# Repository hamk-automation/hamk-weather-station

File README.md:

# hamk-weather-station
cheap ass weather station

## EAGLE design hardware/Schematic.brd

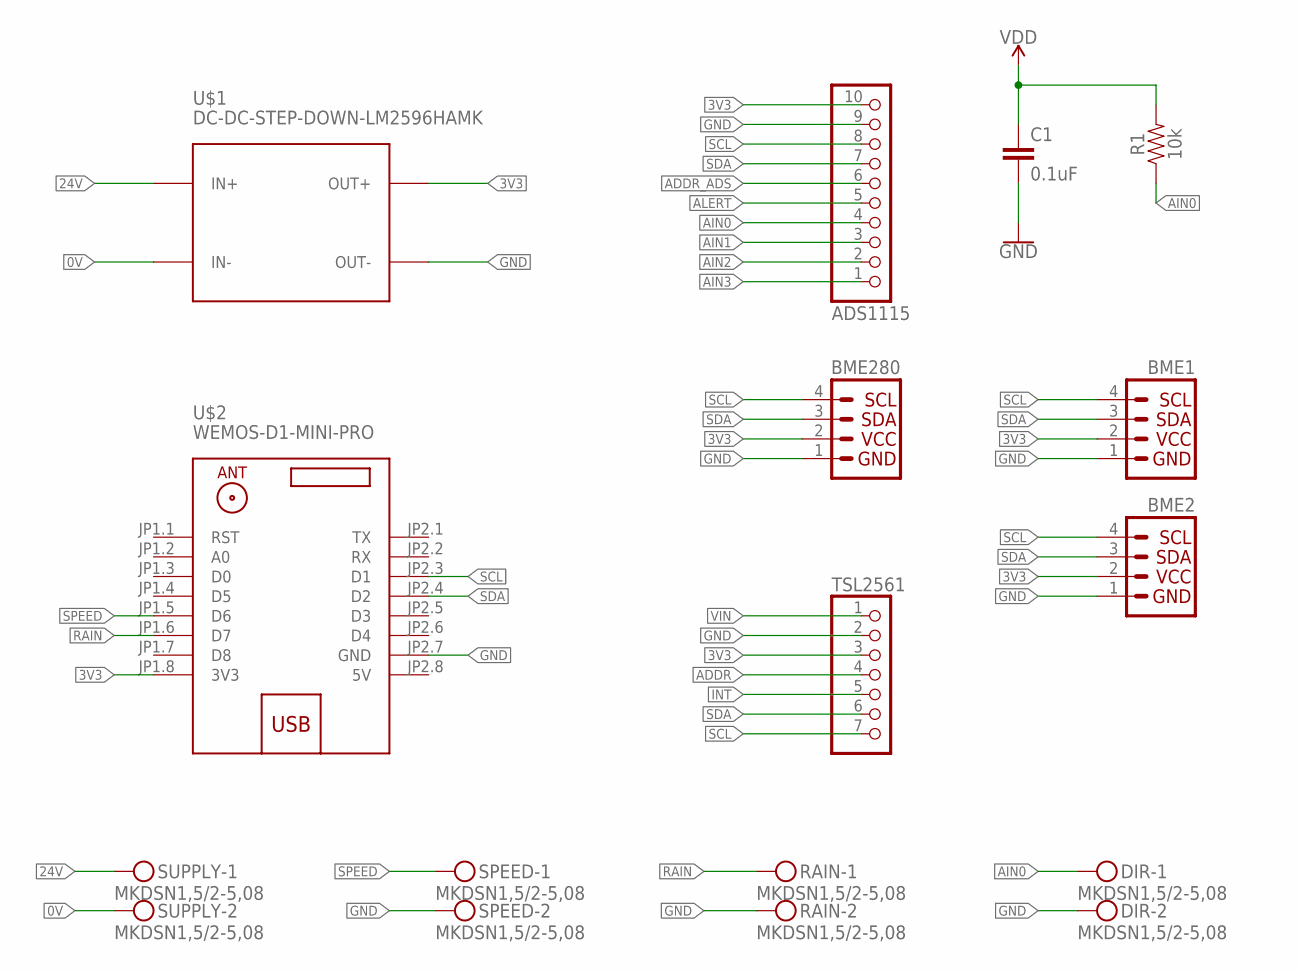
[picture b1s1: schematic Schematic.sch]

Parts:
ADS1115: HEADER-1X1070MIL; 1X10_ROUND70
BME1, BME2, BME280: I2C_STANDARD_NO_SILK; 1X04_NO_SILK
C1: 0.1uF; 0603
DIR: MKDSN1,5/2-5,08
R1: 10k; 0603
RAIN: MKDSN1,5/2-5,08
SPEED: MKDSN1,5/2-5,08
SUPPLY: MKDSN1,5/2-5,08
TSL2561: HEADER-1X7THICKER; 1X07_ROUND_76
U$1: DC-DC-STEP-DOWN-LM2596HAMK; DC-DC-STEP-DOWN-LM2596
U$2: WEMOS-D1-MINI-PRO

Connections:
0V: SUPPLY.2, U$1.IN-
3V3: ADS1115.10, BME1.2, BME2.2, BME280.2, C1.1, R1.2, TSL2561.3, U$1.OUT+, U$2.JP1.8 (3V3)
5V: U$2.JP2.8 (5V)
24V: SUPPLY.1, U$1.IN+
ADDR: TSL2561.4
ADDR_ADS: ADS1115.6
AIN0: ADS1115.4, DIR.1, R1.1
AIN1: ADS1115.3
AIN2: ADS1115.2
AIN3: ADS1115.1
ALERT: ADS1115.5
GND: ADS1115.9, BME1.1, BME2.1, BME280.1, C1.2, DIR.2, RAIN.2, SPEED.2, TSL2561.2, U$1.OUT-, U$2.JP2.7 (GND)
INT: TSL2561.5
RAIN: RAIN.1, U$2.JP1.6 (D7)
SCL: ADS1115.8, BME1.4, BME2.4, BME280.4, TSL2561.7, U$2.JP2.3 (D1)
SDA: ADS1115.7, BME1.3, BME2.3, BME280.3, TSL2561.6, U$2.JP2.4 (D2)
SPEED: SPEED.1, U$2.JP1.5 (D6)
VIN: TSL2561.1

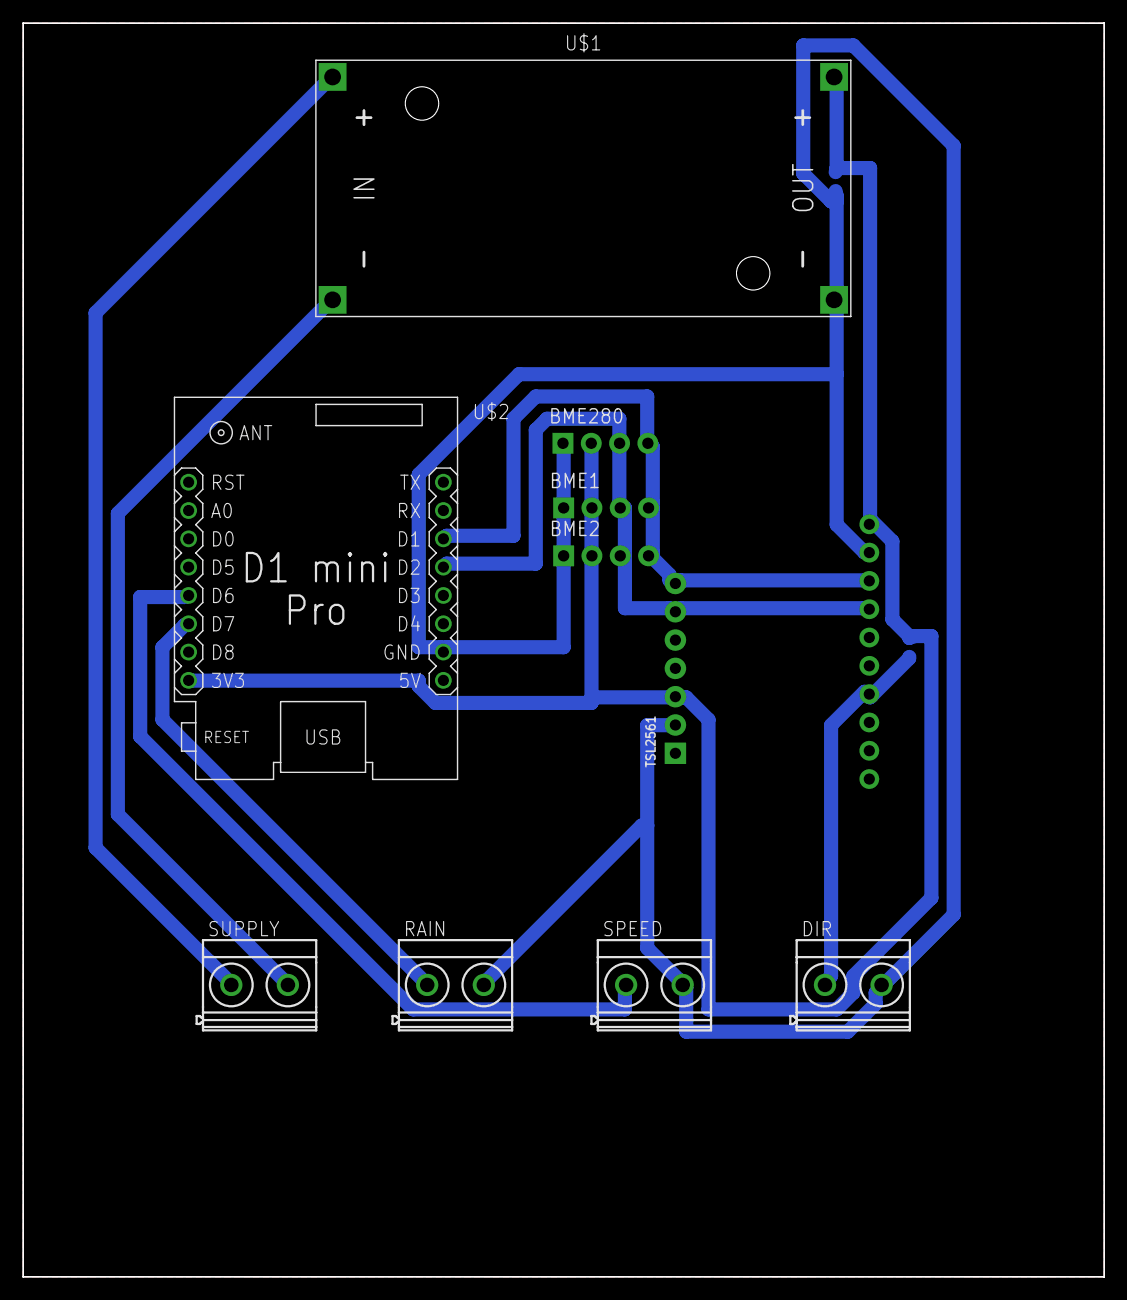
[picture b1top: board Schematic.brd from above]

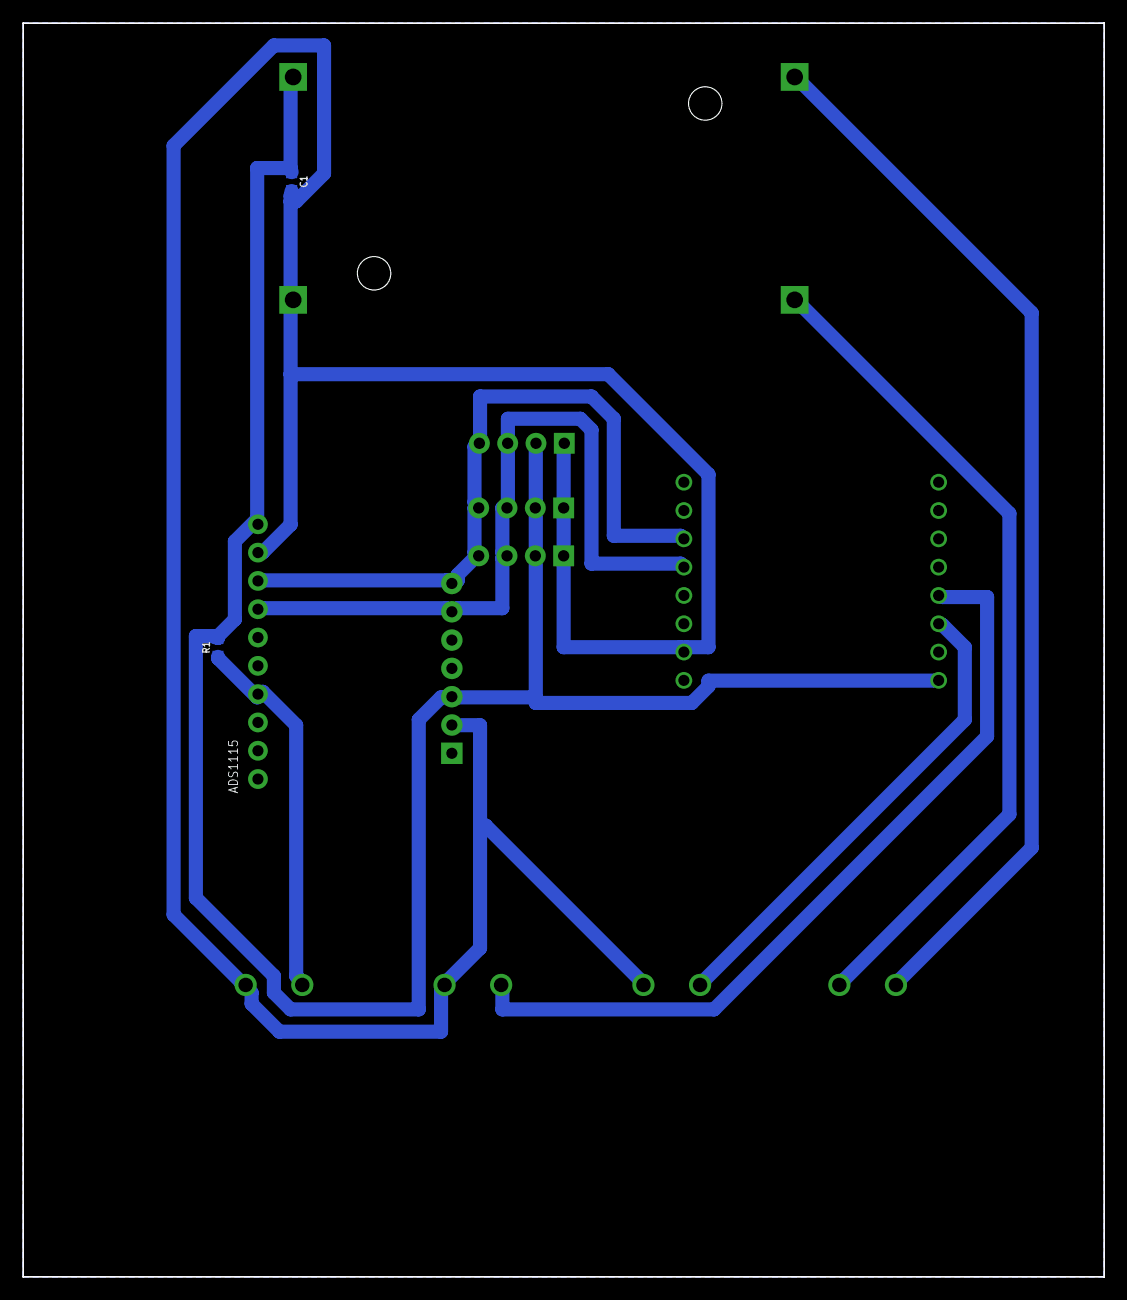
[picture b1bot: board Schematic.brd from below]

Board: 2 copper layers, 97.0 x 112.5 mm, 13 parts (3 on the bottom side), 9 nets.

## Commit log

2017-11-14 nothing to say here
2017-11-14 added irradiance calculations and fixed self heating
2017-11-14 eagle designs

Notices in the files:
parts and their libraries:
microbuilder: This work is placed in the public domain, and may be freely used for commercial and non-commercial work with the following conditions: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
SparkFun-Connectors: Licensing: Creative Commons ShareAlike 4.0 International - https://creativecommons.org/licenses/by-sa/4.0
